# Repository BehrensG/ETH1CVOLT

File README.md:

# ETH1CVOLT
One channel +/- 100V, +/-10V range voltage source

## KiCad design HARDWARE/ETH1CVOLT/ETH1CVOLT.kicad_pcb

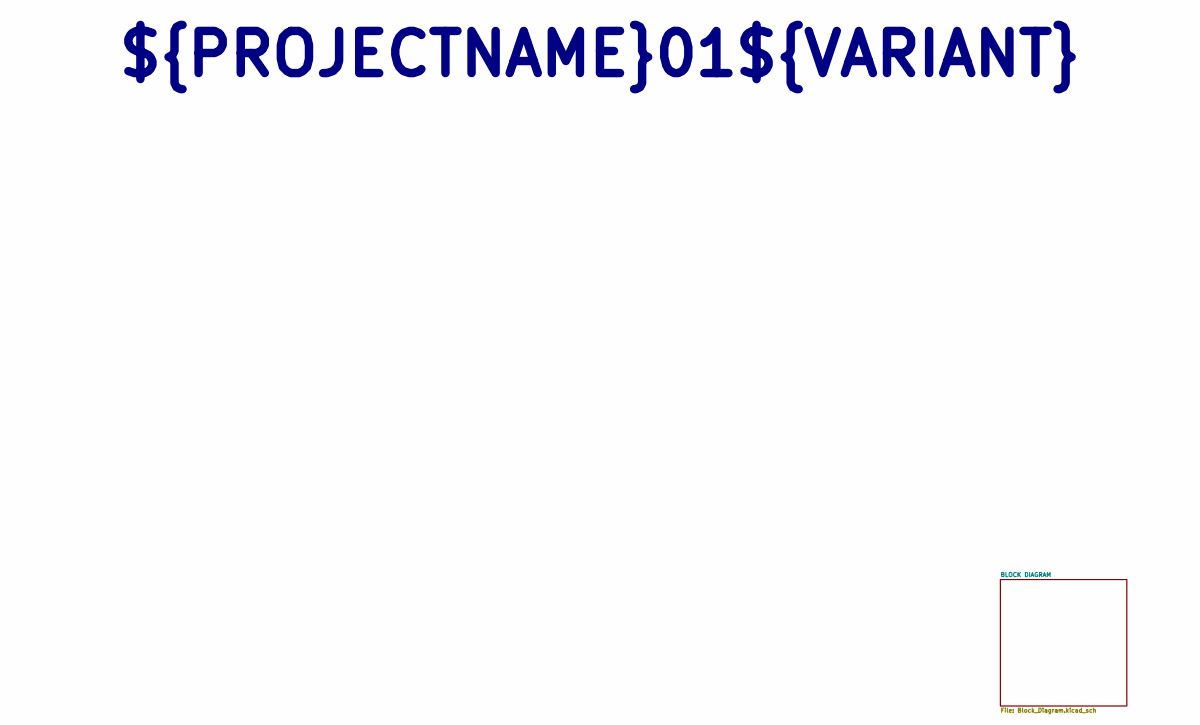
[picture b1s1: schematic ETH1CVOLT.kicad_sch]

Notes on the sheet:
${PROJECTNAME}${REVISION}${VARIANT}

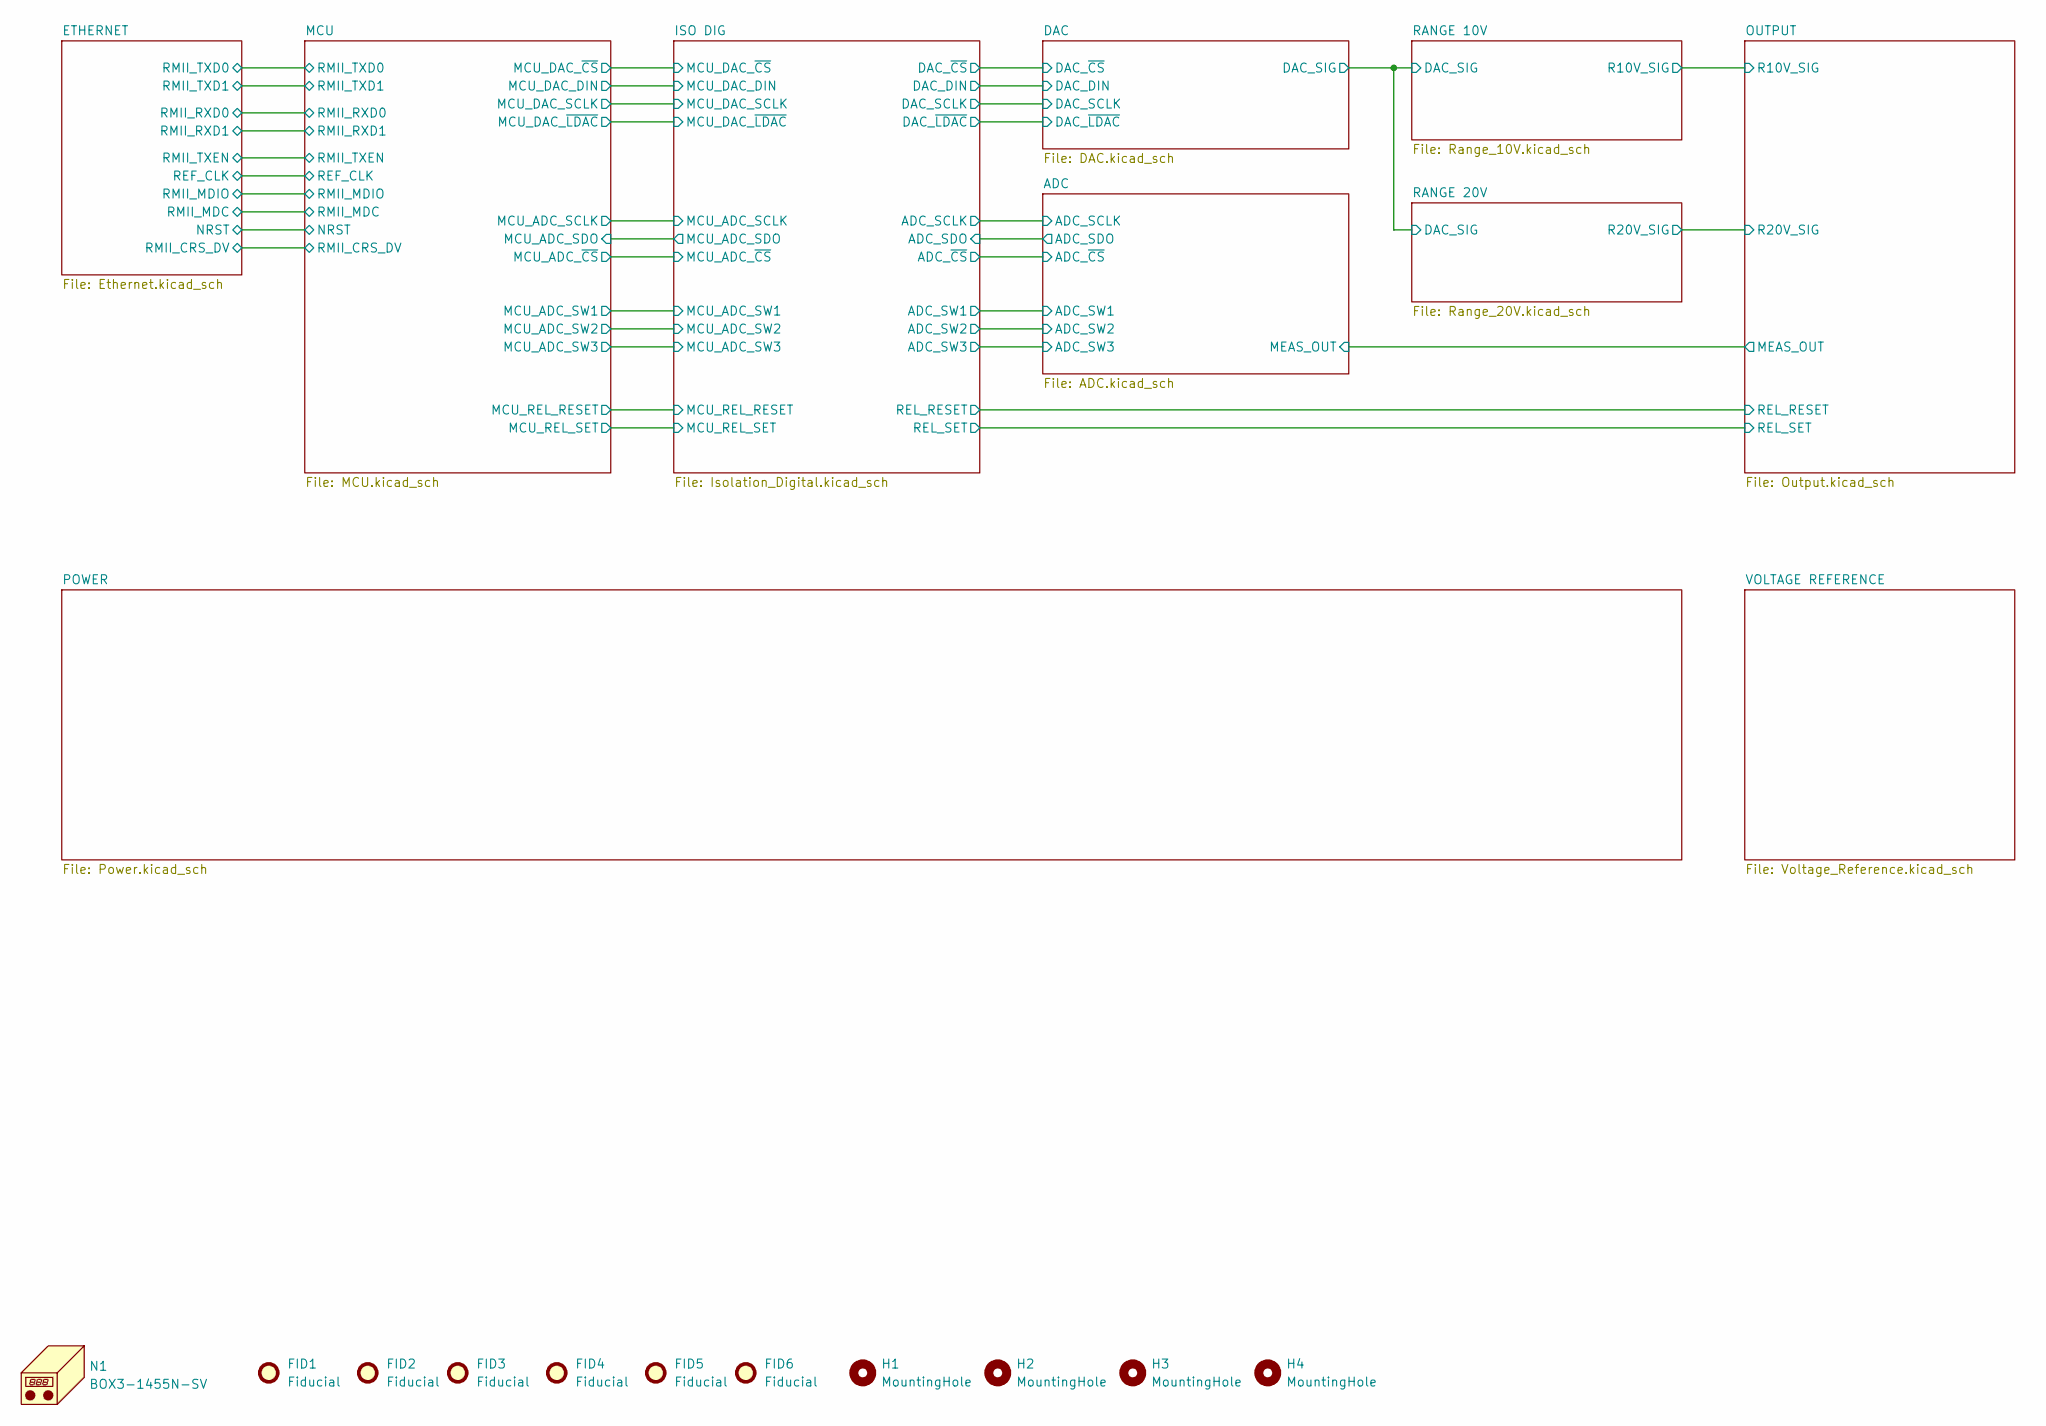
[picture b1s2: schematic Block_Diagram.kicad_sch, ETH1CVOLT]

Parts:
FID1, FID2, FID3, FID4, FID5, FID6: Fiducial; Fiducial_1.5mm_Mask3mm
H1, H2, H3, H4: MountingHole; MountingHole_3.2mm_M3
N1: BOX3-1455N-SV; BOX3-1455N

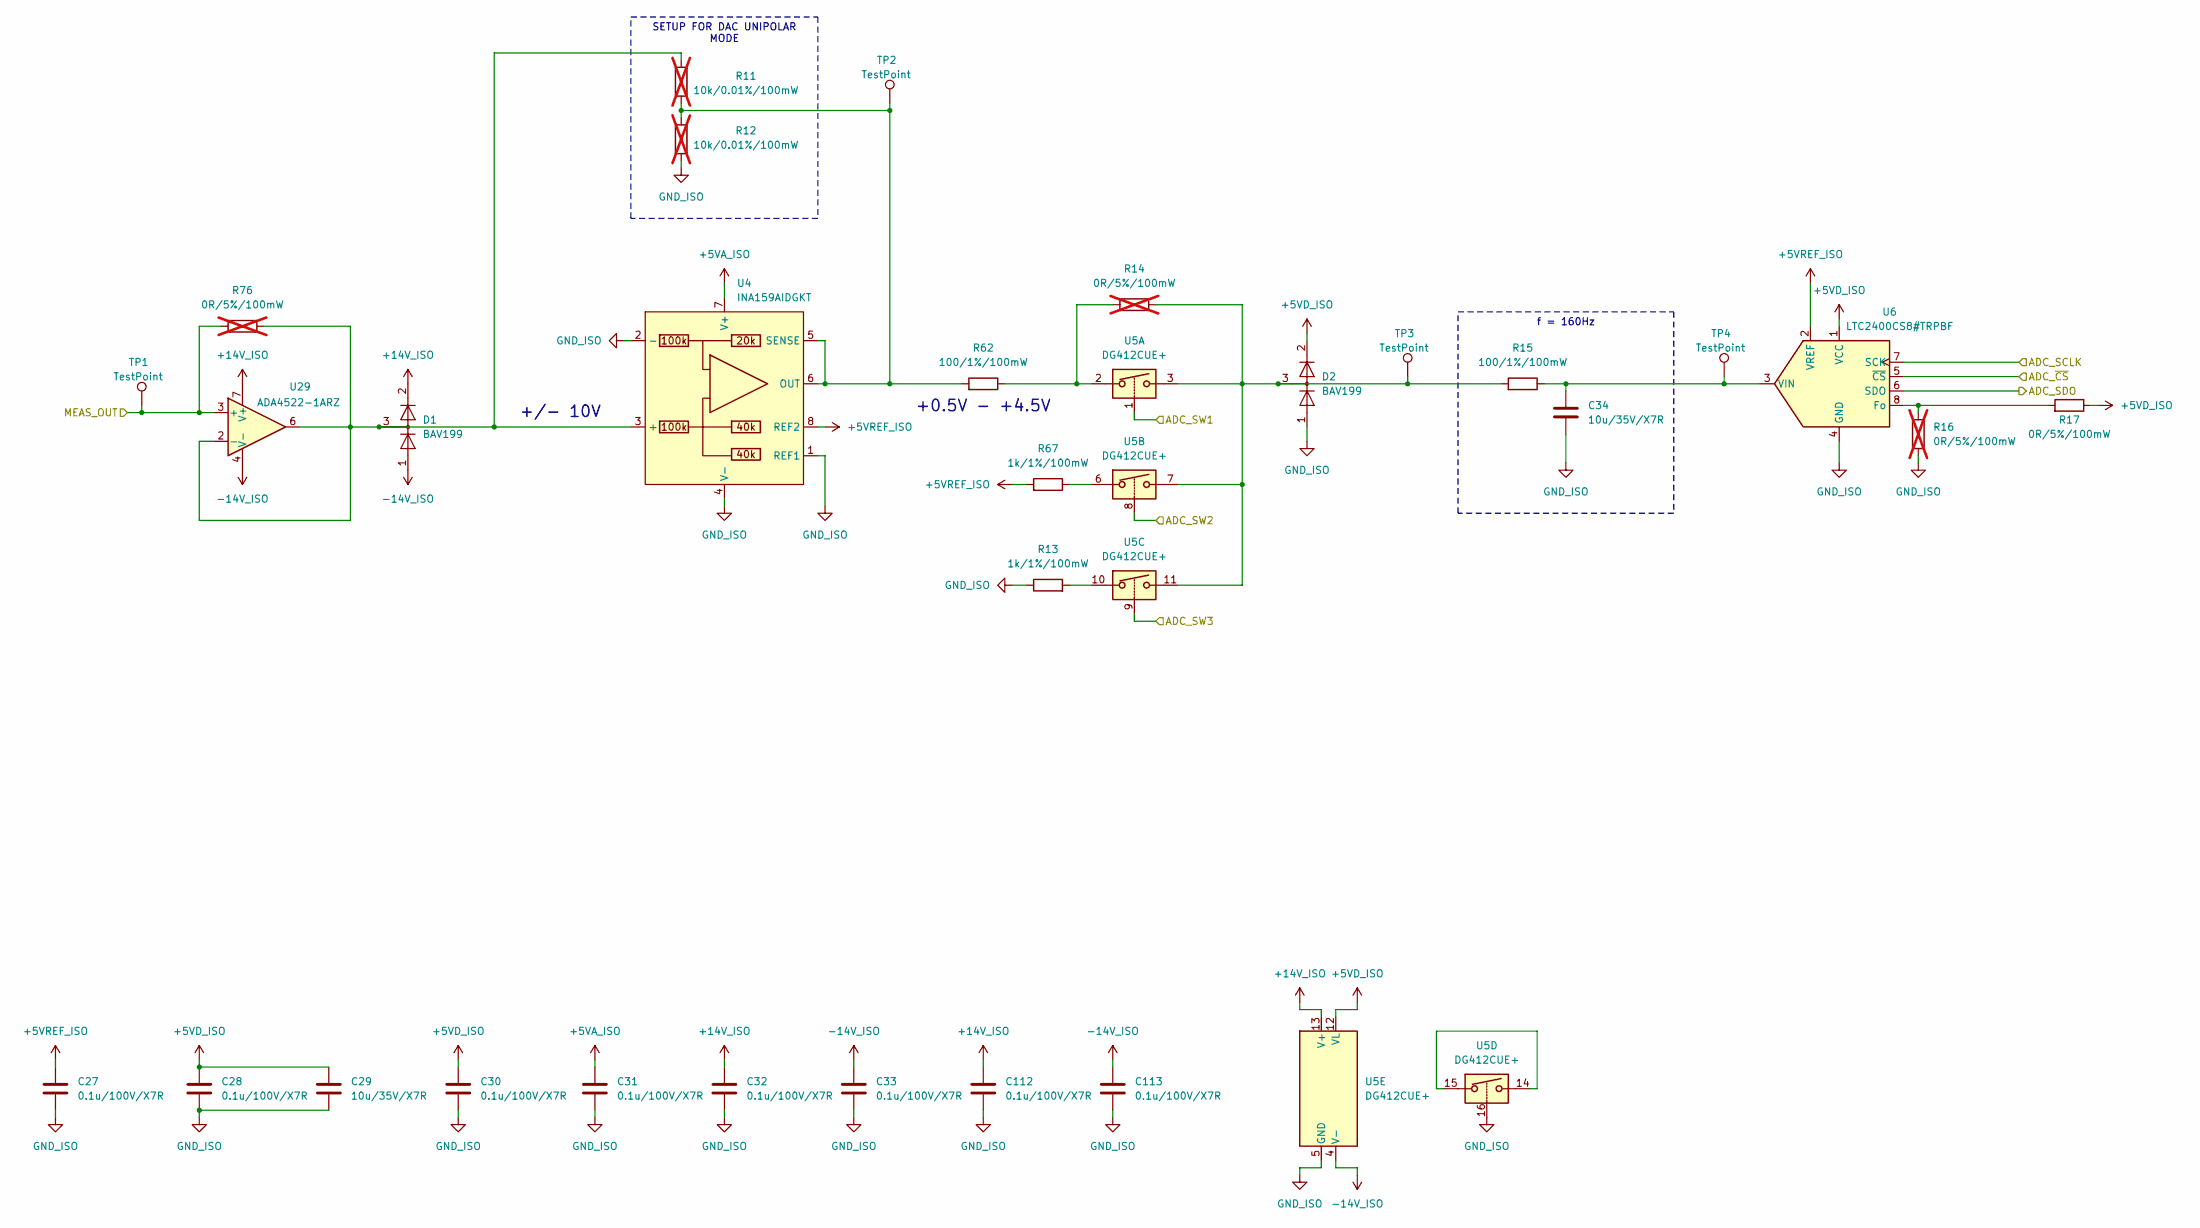
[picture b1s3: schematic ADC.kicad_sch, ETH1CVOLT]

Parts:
C27, C28, C30, C31, C32, C33, C112, C113: 0.1u/100V/X7R; C_0603_1608Metric_Pad1.08x0.95mm_HandSolder
C29, C34: 10u/35V/X7R; C_1206_3216Metric_Pad1.33x1.80mm_HandSolder
D1, D2: BAV199; SOT-23
R11, R12: 10k/0.01%/100mW; R_0603_1608Metric_Pad0.98x0.95mm_HandSolder; not fitted
R13, R67: 1k/1%/100mW; R_0603_1608Metric_Pad0.98x0.95mm_HandSolder
R14, R16, R76: 0R/5%/100mW; R_0603_1608Metric_Pad0.98x0.95mm_HandSolder; not fitted
R15, R62: 100/1%/100mW; R_0603_1608Metric_Pad0.98x0.95mm_HandSolder
R17: 0R/5%/100mW; R_0603_1608Metric_Pad0.98x0.95mm_HandSolder
TP1, TP2, TP3, TP4: TestPoint; TestPoint_Pad_D1.5mm
U4: INA159AIDGKT; VSSOP-8_3x3mm_P0.65mm
U5: DG412CUE+; TSSOP-16_4.4x5mm_P0.65mm
U6: LTC2400CS8#TRPBF; SOIC-8_3.9x4.9mm_P1.27mm
U29: ADA4522-1ARZ; SOIC-8_3.9x4.9mm_P1.27mm

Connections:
+5VA_ISO: C31.1, U4.7 (V+); also elsewhere on the board
+5VD_ISO: C28.1, C29.1, C30.1, D2.2 (A), R17.1, U5.12 (VL), U6.1 (VCC); also elsewhere on the board
+5VREF_ISO: C27.1, R67.2, U4.8 (REF2), U6.2 (VREF); also elsewhere on the board
+14V_ISO: C32.1, C112.1, D1.2 (A), U5.13 (V+), U29.7 (V+); also elsewhere on the board
-14V_ISO: C33.1, C113.1, D1.1 (K), U5.4 (V-), U29.4 (V-); also elsewhere on the board
/BLOCK DIAGRAM/ADC/ADC_SCLK: U6.7 (SCK); also elsewhere on the board
/BLOCK DIAGRAM/ADC/ADC_SDO: U6.6 (SDO); also elsewhere on the board
/BLOCK DIAGRAM/ADC/ADC_SW1: U5.1; also elsewhere on the board
/BLOCK DIAGRAM/ADC/ADC_SW2: U5.8; also elsewhere on the board
/BLOCK DIAGRAM/ADC/ADC_SW3: U5.9; also elsewhere on the board
/BLOCK DIAGRAM/ADC/ADC_~CS: U6.5 (~CS); also elsewhere on the board
/BLOCK DIAGRAM/ADC/MEAS_OUT: R76.1, TP1.1 (1_1), U29.3 (+); also elsewhere on the board
GND_ISO: C27.2, C28.2, C29.2, C30.2, C31.2, C32.2, C33.2, C34.2, C112.2, C113.2, D2.1 (K), R12.1, R13.1, R16.2, U4.1 (REF1), U4.2 (-), U4.4 (V-), U5.5 (GND), U5.16, U6.4 (GND); also elsewhere on the board
unnamed: D2.3 (K), R14.2, R15.2, TP3.1 (1_1), U5.3, U5.7, U5.11
unnamed: R13.2, U5.10
unnamed: R14.1, R62.1, U5.2
unnamed: R67.1, U5.6
unnamed: R11.1, R12.2, R62.2, TP2.1 (1_1), U4.5 (SENSE), U4.6 (OUT)
unnamed: U5.14, U5.15
unnamed: R16.1, R17.2, U6.8 (Fo)
unnamed: C34.1, R15.1, TP4.1 (1_1), U6.3 (VIN)
unnamed: D1.3 (K), R11.2, R76.2, U4.3 (+), U29.2 (-), U29.6

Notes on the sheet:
+/- 10V
+0.5V - +4.5V
f = 160Hz
SETUP FOR DAC UNIPOLAR MODE

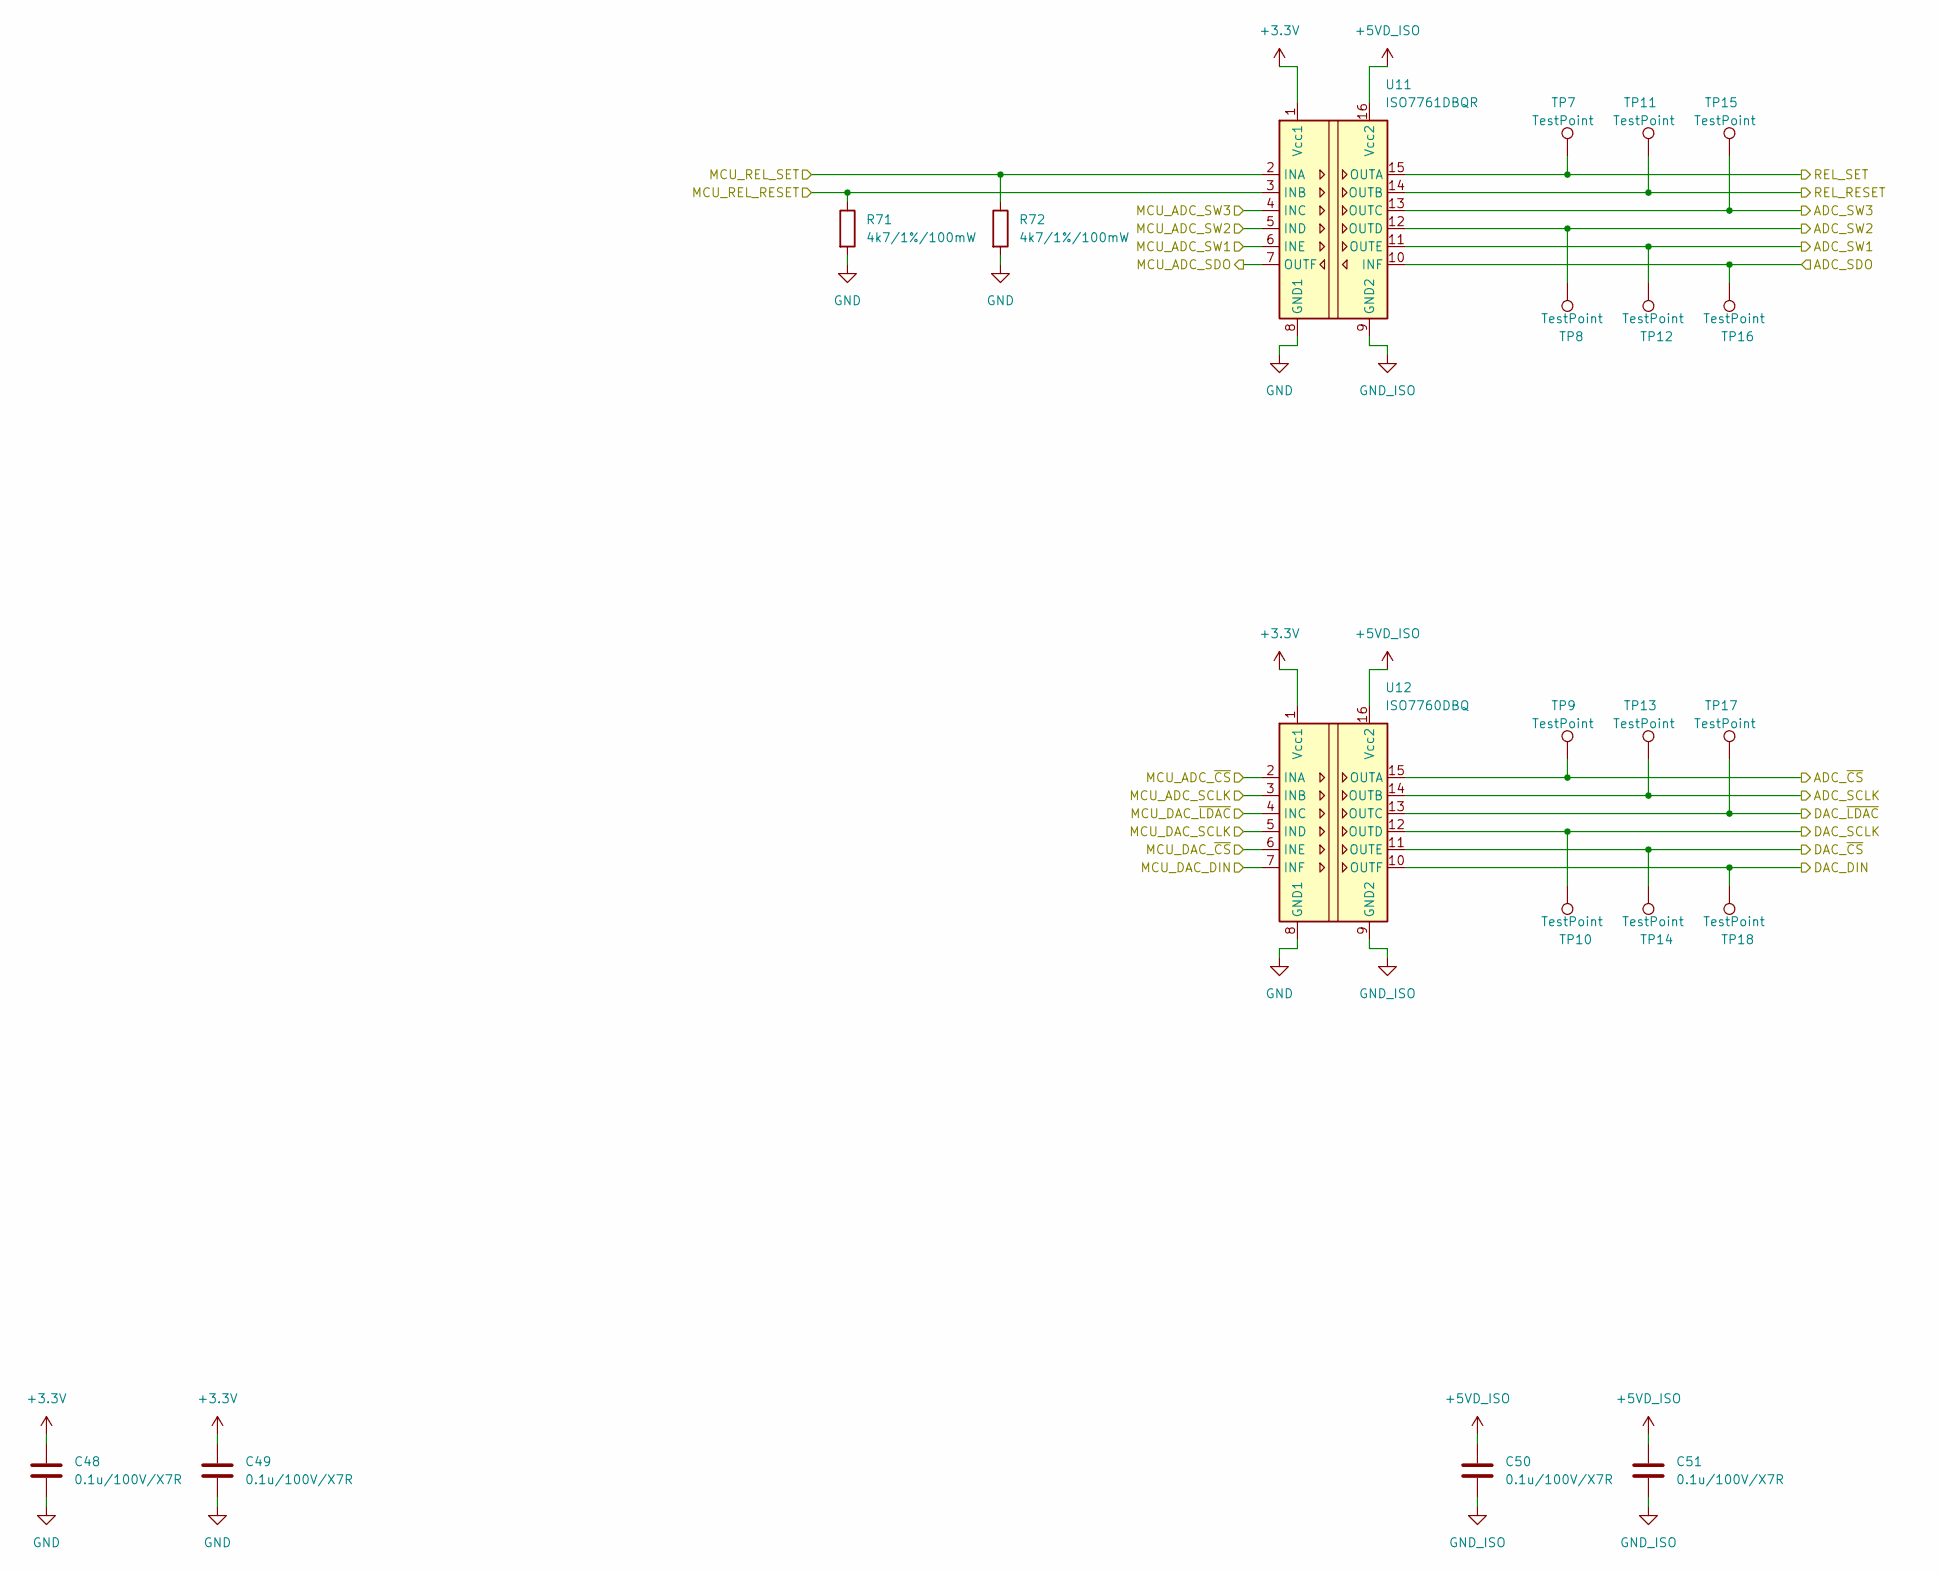
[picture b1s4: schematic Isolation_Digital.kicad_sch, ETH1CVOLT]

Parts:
C48, C49, C50, C51: 0.1u/100V/X7R; C_0603_1608Metric_Pad1.08x0.95mm_HandSolder
R71, R72: 4k7/1%/100mW; R_0603_1608Metric_Pad0.98x0.95mm_HandSolder
TP7, TP8, TP9, TP10, TP11, TP12, TP13, TP14, TP15, TP16, TP17, TP18: TestPoint; TestPoint_Pad_D1.0mm
U11: ISO7761DBQR; SSOP-16_3.9x4.9mm_P0.635mm
U12: ISO7760DBQ; SSOP-16_3.9x4.9mm_P0.635mm

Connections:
+3.3V: C48.1, C49.1, U11.1 (Vcc1), U12.1 (Vcc1); also elsewhere on the board
+5VD_ISO: C50.1, C51.1, U11.16 (Vcc2), U12.16 (Vcc2); also elsewhere on the board
/BLOCK DIAGRAM/ADC/ADC_SCLK: TP13.1 (1_1), U12.14 (OUTB); also elsewhere on the board
/BLOCK DIAGRAM/ADC/ADC_SDO: TP16.1 (1_1), U11.10 (INF); also elsewhere on the board
/BLOCK DIAGRAM/ADC/ADC_SW1: TP12.1 (1_1), U11.11 (OUTE); also elsewhere on the board
/BLOCK DIAGRAM/ADC/ADC_SW2: TP8.1 (1_1), U11.12 (OUTD); also elsewhere on the board
/BLOCK DIAGRAM/ADC/ADC_SW3: TP15.1 (1_1), U11.13 (OUTC); also elsewhere on the board
/BLOCK DIAGRAM/ADC/ADC_~CS: TP9.1 (1_1), U12.15 (OUTA); also elsewhere on the board
/BLOCK DIAGRAM/DAC/DAC_DIN: TP18.1 (1_1), U12.10 (OUTF); also elsewhere on the board
/BLOCK DIAGRAM/DAC/DAC_SCLK: TP10.1 (1_1), U12.12 (OUTD); also elsewhere on the board
/BLOCK DIAGRAM/DAC/DAC_~CS: TP14.1 (1_1), U12.11 (OUTE); also elsewhere on the board
/BLOCK DIAGRAM/DAC/DAC_~LDAC: TP17.1 (1_1), U12.13 (OUTC); also elsewhere on the board
/BLOCK DIAGRAM/ISO DIG/MCU_ADC_SCLK: U12.3 (INB); also elsewhere on the board
/BLOCK DIAGRAM/ISO DIG/MCU_ADC_SDO: U11.7 (OUTF); also elsewhere on the board
/BLOCK DIAGRAM/ISO DIG/MCU_ADC_SW1: U11.6 (INE); also elsewhere on the board
/BLOCK DIAGRAM/ISO DIG/MCU_ADC_SW2: U11.5 (IND); also elsewhere on the board
/BLOCK DIAGRAM/ISO DIG/MCU_ADC_SW3: U11.4 (INC); also elsewhere on the board
/BLOCK DIAGRAM/ISO DIG/MCU_ADC_~CS: U12.2 (INA); also elsewhere on the board
/BLOCK DIAGRAM/ISO DIG/MCU_DAC_DIN: U12.7 (INF); also elsewhere on the board
/BLOCK DIAGRAM/ISO DIG/MCU_DAC_SCLK: U12.5 (IND); also elsewhere on the board
/BLOCK DIAGRAM/ISO DIG/MCU_DAC_~CS: U12.6 (INE); also elsewhere on the board
/BLOCK DIAGRAM/ISO DIG/MCU_DAC_~LDAC: U12.4 (INC); also elsewhere on the board
/BLOCK DIAGRAM/ISO DIG/MCU_REL_RESET: R71.1, U11.3 (INB); also elsewhere on the board
/BLOCK DIAGRAM/ISO DIG/MCU_REL_SET: R72.1, U11.2 (INA); also elsewhere on the board
/BLOCK DIAGRAM/ISO DIG/REL_RESET: TP11.1 (1_1), U11.14 (OUTB); also elsewhere on the board
/BLOCK DIAGRAM/ISO DIG/REL_SET: TP7.1 (1_1), U11.15 (OUTA); also elsewhere on the board
GND: C48.2, C49.2, R71.2, R72.2, U11.8 (GND1), U12.8 (GND1); also elsewhere on the board
GND_ISO: C50.2, C51.2, U11.9 (GND2), U12.9 (GND2); also elsewhere on the board

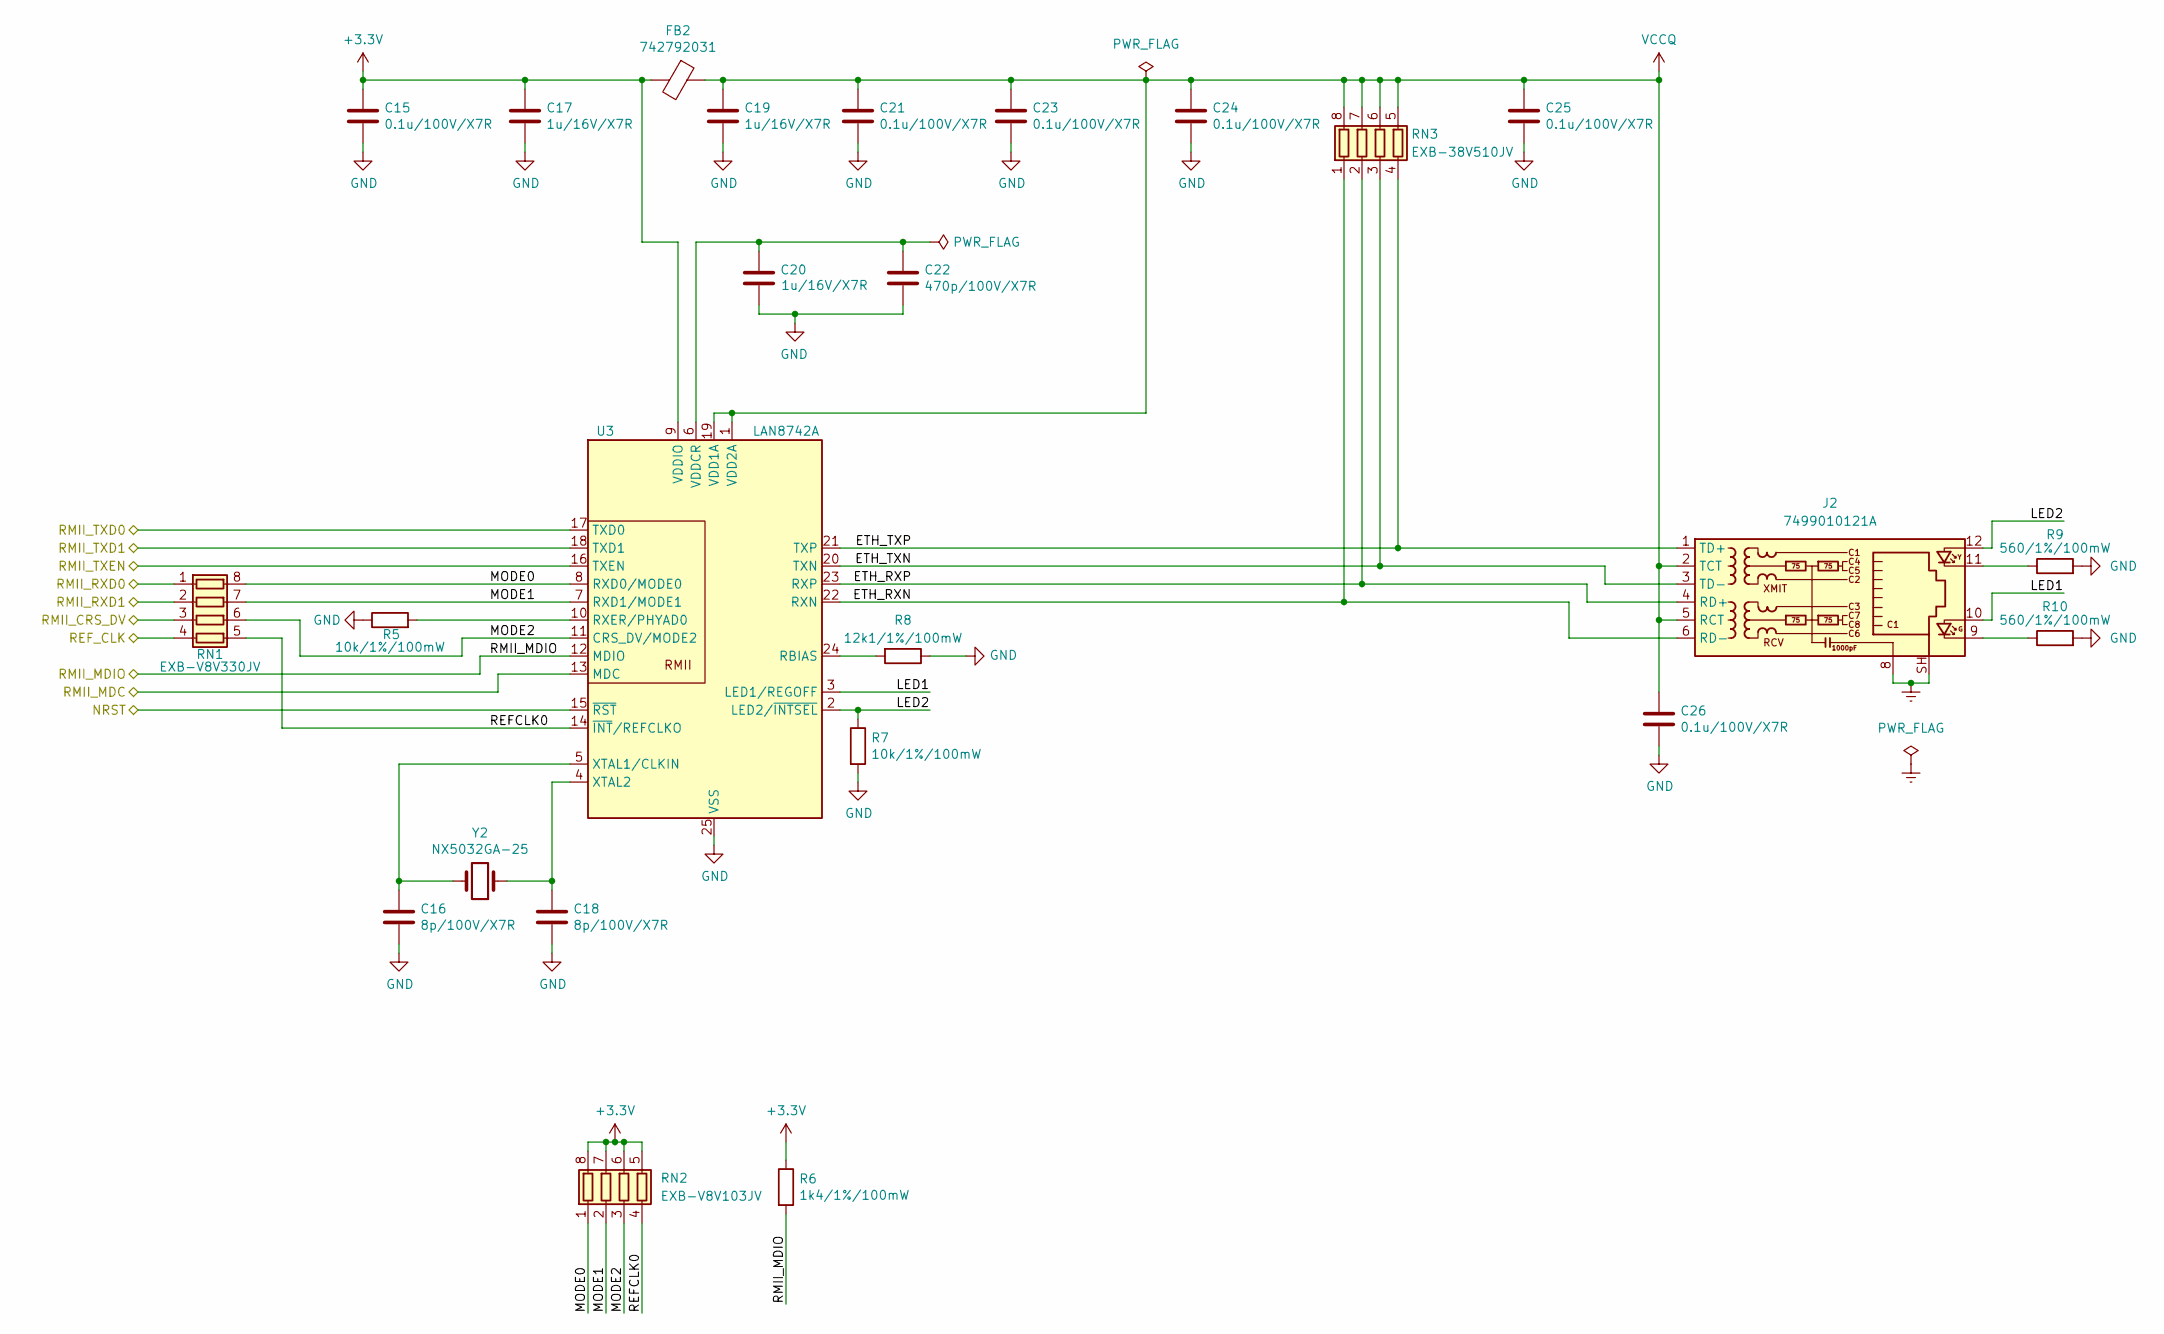
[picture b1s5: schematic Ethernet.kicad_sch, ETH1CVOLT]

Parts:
C15, C21, C23, C24, C25, C26: 0.1u/100V/X7R; C_0603_1608Metric_Pad1.08x0.95mm_HandSolder
C16, C18: 8p/100V/X7R; C_0603_1608Metric_Pad1.08x0.95mm_HandSolder
C17, C19, C20: 1u/16V/X7R; C_0603_1608Metric_Pad1.08x0.95mm_HandSolder
C22: 470p/100V/X7R; C_0603_1608Metric_Pad1.08x0.95mm_HandSolder
FB2: 742792031; L_0805_2012Metric_Pad1.05x1.20mm_HandSolder
J2: 7499010121A; RJ45_Wuerth_7499010121A_Horizontal
R5, R7: 10k/1%/100mW; R_0603_1608Metric_Pad0.98x0.95mm_HandSolder
R6: 1k4/1%/100mW; R_0603_1608Metric_Pad0.98x0.95mm_HandSolder
R8: 12k1/1%/100mW; R_0603_1608Metric_Pad0.98x0.95mm_HandSolder
R9, R10: 560/1%/100mW; R_0603_1608Metric_Pad0.98x0.95mm_HandSolder
RN1: EXB-V8V330JV; R_Array_Convex_4x0603
RN2: EXB-V8V103JV; R_Array_Convex_4x0603
RN3: EXB-38V510JV; R_Array_Convex_4x0603
U3: LAN8742A; VQFN-24-1EP_4x4mm_P0.5mm_EP2.5x2.5mm_ThermalVias
Y2: NX5032GA-25; NX5032GA

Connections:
+3.3V: C15.1, C17.1, FB2.2, R6.1, RN2.5 (R4.2), RN2.6 (R3.2), RN2.7 (R2.2), RN2.8 (R1.2), U3.9 (VDDIO); also elsewhere on the board
/BLOCK DIAGRAM/ETHERNET/ETH_RXN: J2.6 (RD-), RN3.1 (R1.1), U3.22 (RXN)
/BLOCK DIAGRAM/ETHERNET/ETH_RXP: J2.4 (RD+), RN3.2 (R2.1), U3.23 (RXP)
/BLOCK DIAGRAM/ETHERNET/ETH_TXN: J2.3 (TD-), RN3.3 (R3.1), U3.20 (TXN)
/BLOCK DIAGRAM/ETHERNET/ETH_TXP: J2.1 (TD+), RN3.4 (R4.1), U3.21 (TXP)
/BLOCK DIAGRAM/ETHERNET/LED1: J2.10, U3.3 (LED1/REGOFF)
/BLOCK DIAGRAM/ETHERNET/LED2: J2.12, R7.1, U3.2 (LED2/~INTSEL)
/BLOCK DIAGRAM/ETHERNET/MODE0: RN1.8 (R1.2), RN2.1 (R1.1), U3.8 (RXD0/MODE0)
/BLOCK DIAGRAM/ETHERNET/MODE1: RN1.7 (R2.2), RN2.2 (R2.1), U3.7 (RXD1/MODE1)
/BLOCK DIAGRAM/ETHERNET/MODE2: RN1.6 (R3.2), RN2.3 (R3.1), U3.11 (CRS_DV/MODE2)
/BLOCK DIAGRAM/ETHERNET/REFCLK0: RN1.5 (R4.2), RN2.4 (R4.1), U3.14 (~INT/REFCLKO)
/BLOCK DIAGRAM/ETHERNET/REF_CLK: RN1.4 (R4.1); also elsewhere on the board
/BLOCK DIAGRAM/ETHERNET/RMII_CRS_DV: RN1.3 (R3.1); also elsewhere on the board
/BLOCK DIAGRAM/ETHERNET/RMII_MDC: U3.13 (MDC); also elsewhere on the board
/BLOCK DIAGRAM/ETHERNET/RMII_MDIO: R6.2, U3.12 (MDIO); also elsewhere on the board
/BLOCK DIAGRAM/ETHERNET/RMII_RXD0: RN1.1 (R1.1); also elsewhere on the board
/BLOCK DIAGRAM/ETHERNET/RMII_RXD1: RN1.2 (R2.1); also elsewhere on the board
/BLOCK DIAGRAM/ETHERNET/RMII_TXD0: U3.17 (TXD0); also elsewhere on the board
/BLOCK DIAGRAM/ETHERNET/RMII_TXD1: U3.18 (TXD1); also elsewhere on the board
/BLOCK DIAGRAM/ETHERNET/RMII_TXEN: U3.16 (TXEN); also elsewhere on the board
/BLOCK DIAGRAM/MCU/NRST: U3.15 (~RST); also elsewhere on the board
Earth: J2.8, J2.SH
GND: C15.2, C16.2, C17.2, C18.2, C19.2, C20.2, C21.2, C22.2, C23.2, C24.2, C25.2, C26.2, R5.1, R7.2, R8.1, R9.2, R10.2, U3.25 (VSS); also elsewhere on the board
unnamed: J2.9, R10.1
unnamed: J2.11, R9.1
unnamed: R8.2, U3.24 (RBIAS)
unnamed: R5.2, U3.10 (RXER/PHYAD0)
unnamed: C20.1, C22.1, U3.6 (VDDCR)
unnamed: C16.1, U3.5 (XTAL1/CLKIN), Y2.2
unnamed: C18.1, U3.4 (XTAL2), Y2.1
VCCQ: C19.1, C21.1, C23.1, C24.1, C25.1, C26.1, FB2.1, J2.2 (TCT), J2.5 (RCT), RN3.5 (R4.2), RN3.6 (R3.2), RN3.7 (R2.2), RN3.8 (R1.2), U3.1 (VDD2A), U3.19 (VDD1A)

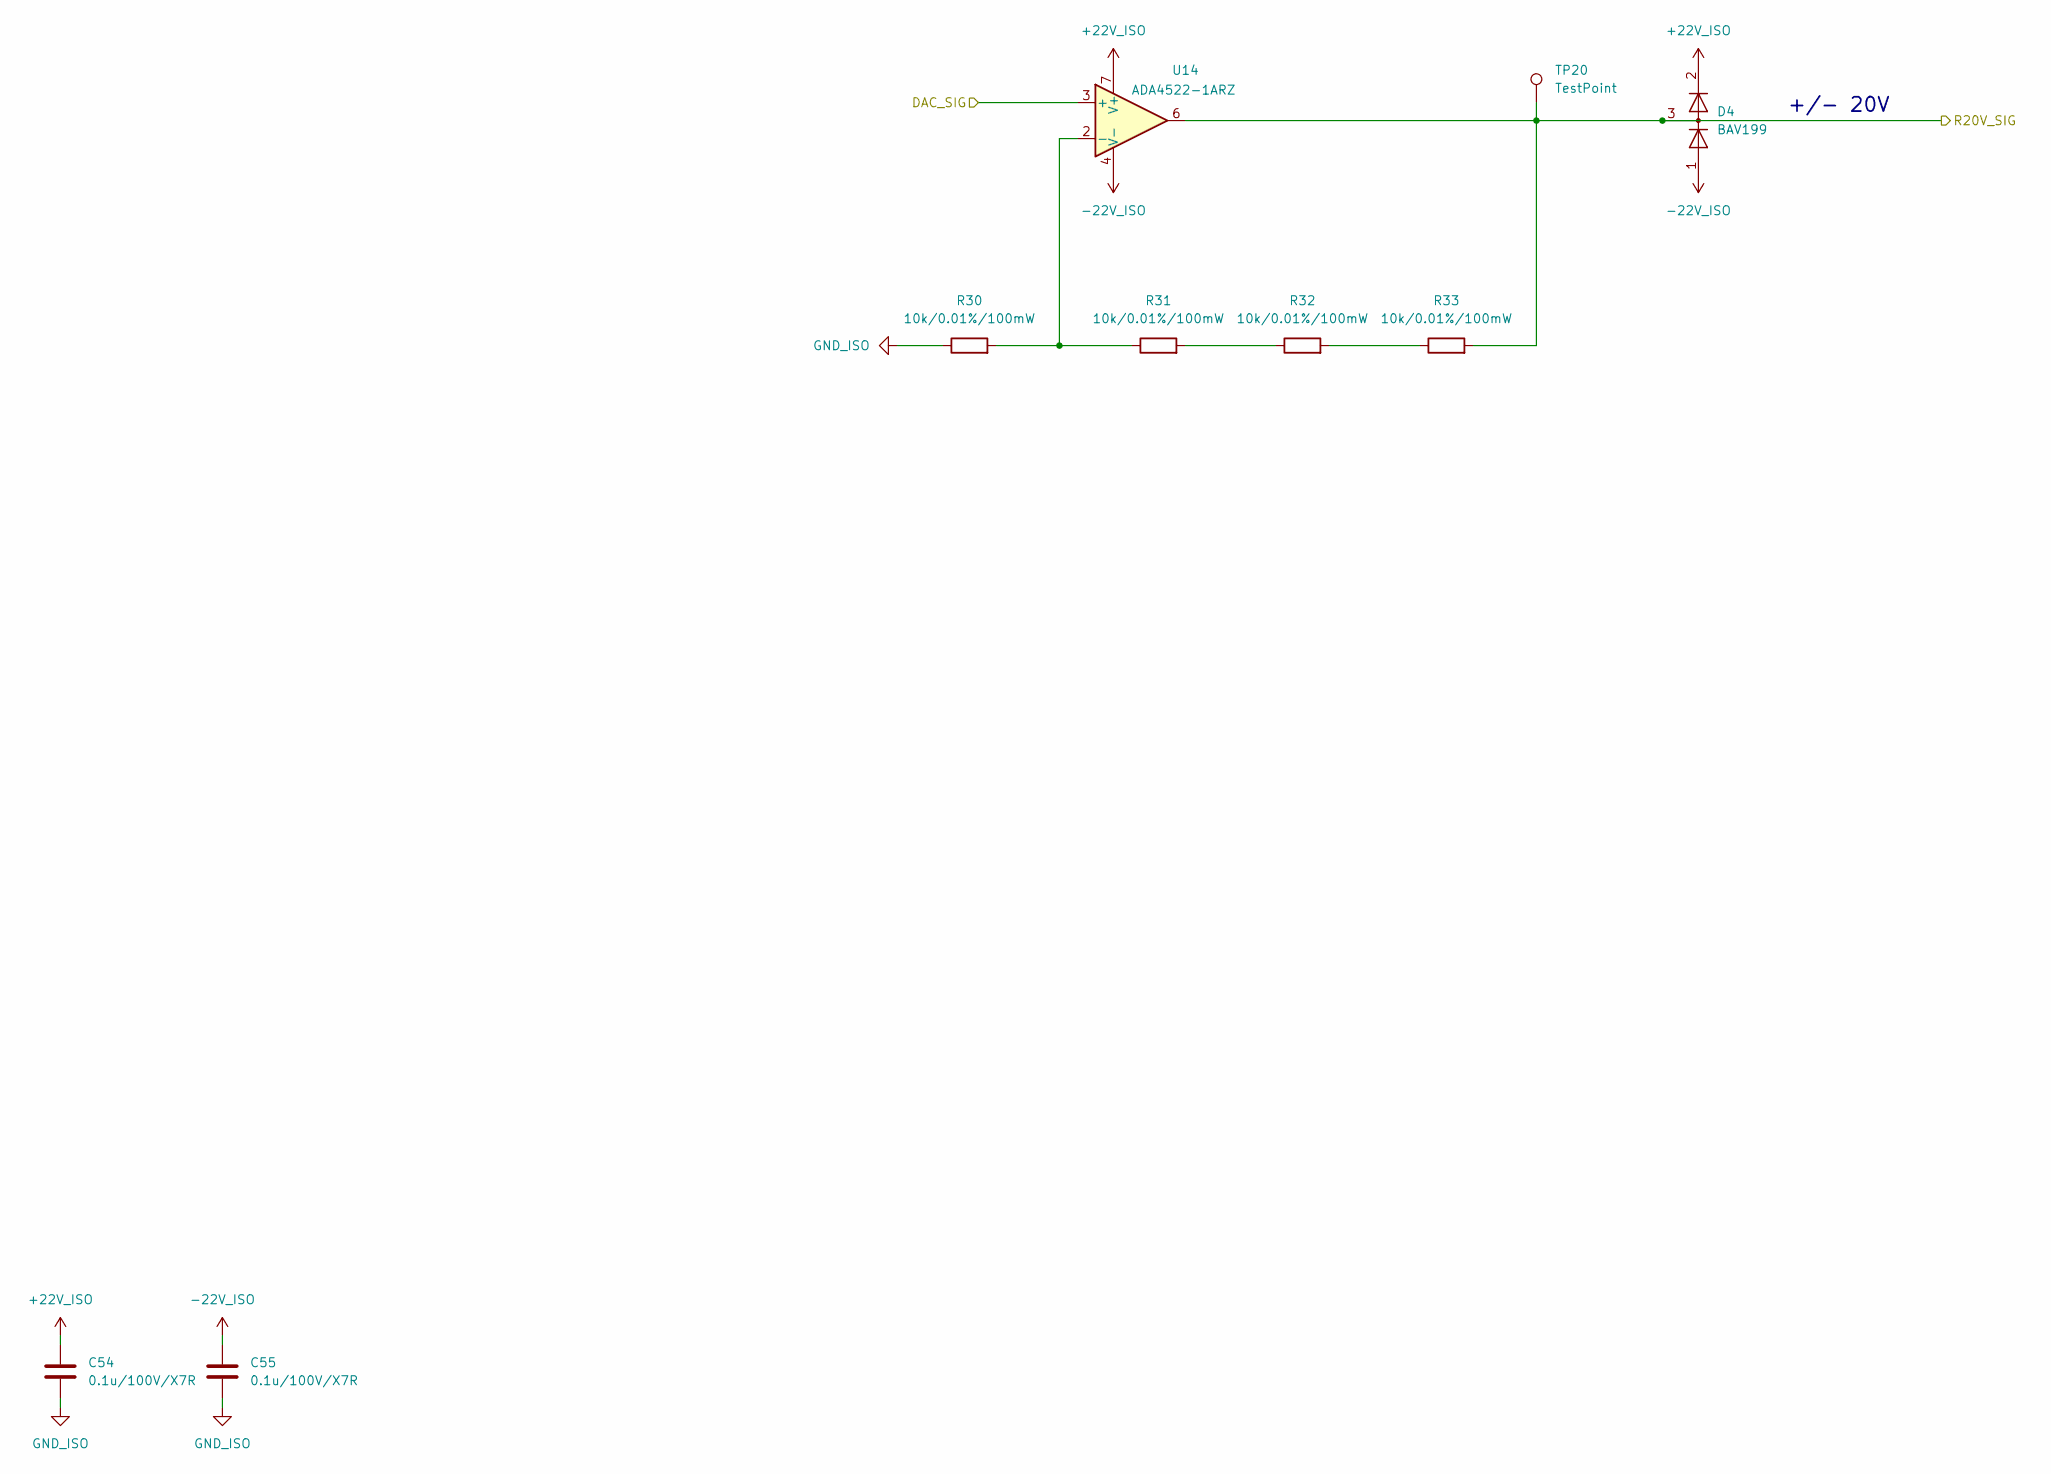
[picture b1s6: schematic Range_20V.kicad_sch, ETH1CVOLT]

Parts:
C54, C55: 0.1u/100V/X7R; C_0603_1608Metric_Pad1.08x0.95mm_HandSolder
D4: BAV199; SOT-23
R30, R31, R32, R33: 10k/0.01%/100mW; R_0603_1608Metric_Pad0.98x0.95mm_HandSolder
TP20: TestPoint; TestPoint_Pad_D1.5mm
U14: ADA4522-1ARZ; SOIC-8_3.9x4.9mm_P1.27mm

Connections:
+22V_ISO: C54.1, D4.2 (A), U14.7 (V+); also elsewhere on the board
-22V_ISO: C55.1, D4.1 (K), U14.4 (V-); also elsewhere on the board
/BLOCK DIAGRAM/DAC/DAC_SIG: U14.3 (+); also elsewhere on the board
/BLOCK DIAGRAM/OUTPUT/R20V_SIG: D4.3 (K), R33.2, TP20.1 (1_1), U14.6; also elsewhere on the board
GND_ISO: C54.2, C55.2, R30.1; also elsewhere on the board
unnamed: R31.2, R32.1
unnamed: R32.2, R33.1
unnamed: R30.2, R31.1, U14.2 (-)

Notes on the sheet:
+/- 20V
